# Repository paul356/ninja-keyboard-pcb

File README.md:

# How to use this project?

This pcb use some symbols and footprints that are not in the default KiCad library. I think the fp cache feature should cache these symbols and footprints. But in case you need them.
1. Keyswitch Kicad Library
2. Additional symbols and footprints are in the folder "user_added".

## 3D Case Design

A FreeCAD 3D model of the keyboard case is included in this project: `keyboard-case.FCStd`. You can open it with [FreeCAD](https://www.freecad.org/) to view, modify, or export the case design for 3D printing or CNC machining.

## License

This project is licensed under the [GNU General Public License v3.0](LICENSE).

You are free to use, study, modify, and distribute this project, provided that any derivative works are also distributed under the same GPL-3.0 license.

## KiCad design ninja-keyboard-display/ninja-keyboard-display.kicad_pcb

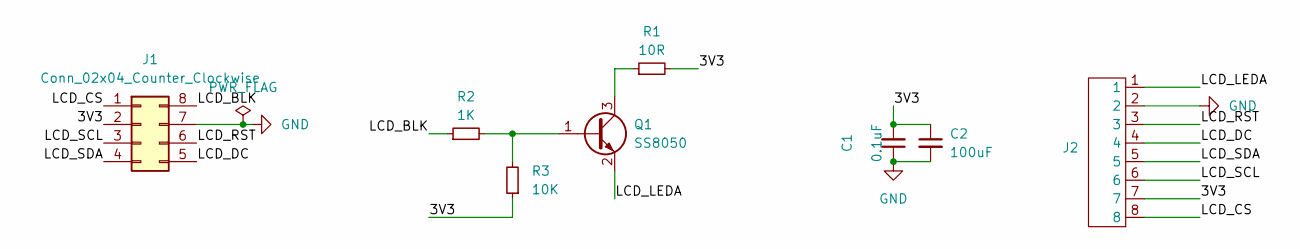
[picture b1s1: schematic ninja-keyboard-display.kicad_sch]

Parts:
C1: 0.1uF; C_0603_1608Metric; LCSC Part # C14663
C2: 100uF; CP_Elec_6.3x7.7
J1: Conn_02x04_Counter_Clockwise; PinHeader_2x04_P2.54mm_Vertical
J2: HanElectricity 1x8 P0.5mm drawer up-side; LCSC Part # C5362163
Q1: SS8050; SOT-23; LCSC Part # C2150
R1: 10R; R_0603_1608Metric; LCSC Part # C22859
R2: 1K; R_0603_1608Metric; LCSC Part # C21190
R3: 10K; R_0603_1608Metric; LCSC Part # C25804

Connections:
/3V3: C1.2, C2.1, J1.2, J2.7, R1.2, R3.1
/LCD_BLK: J1.8, R2.1
/LCD_CS: J1.1, J2.8
/LCD_DC: J1.5, J2.4
/LCD_LEDA: J2.1, Q1.2 (E)
/LCD_RST: J1.6, J2.3
/LCD_SCL: J1.3, J2.6
/LCD_SDA: J1.4, J2.5
GND: C1.1, C2.2, J1.7, J2.2
unnamed: Q1.1 (B), R2.2, R3.2
unnamed: Q1.3 (C), R1.1

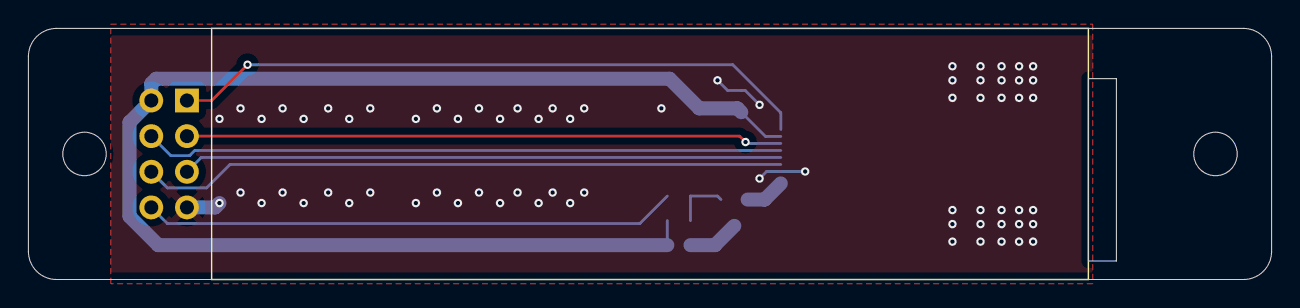
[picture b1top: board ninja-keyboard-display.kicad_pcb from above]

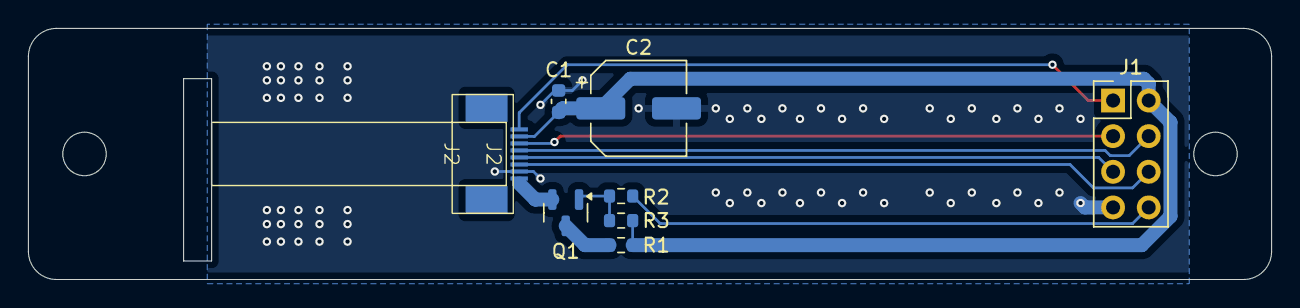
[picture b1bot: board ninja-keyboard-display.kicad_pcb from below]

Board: 2 copper layers, 88.6 x 17.9 mm, 8 parts (8 on the bottom side), 11 nets.

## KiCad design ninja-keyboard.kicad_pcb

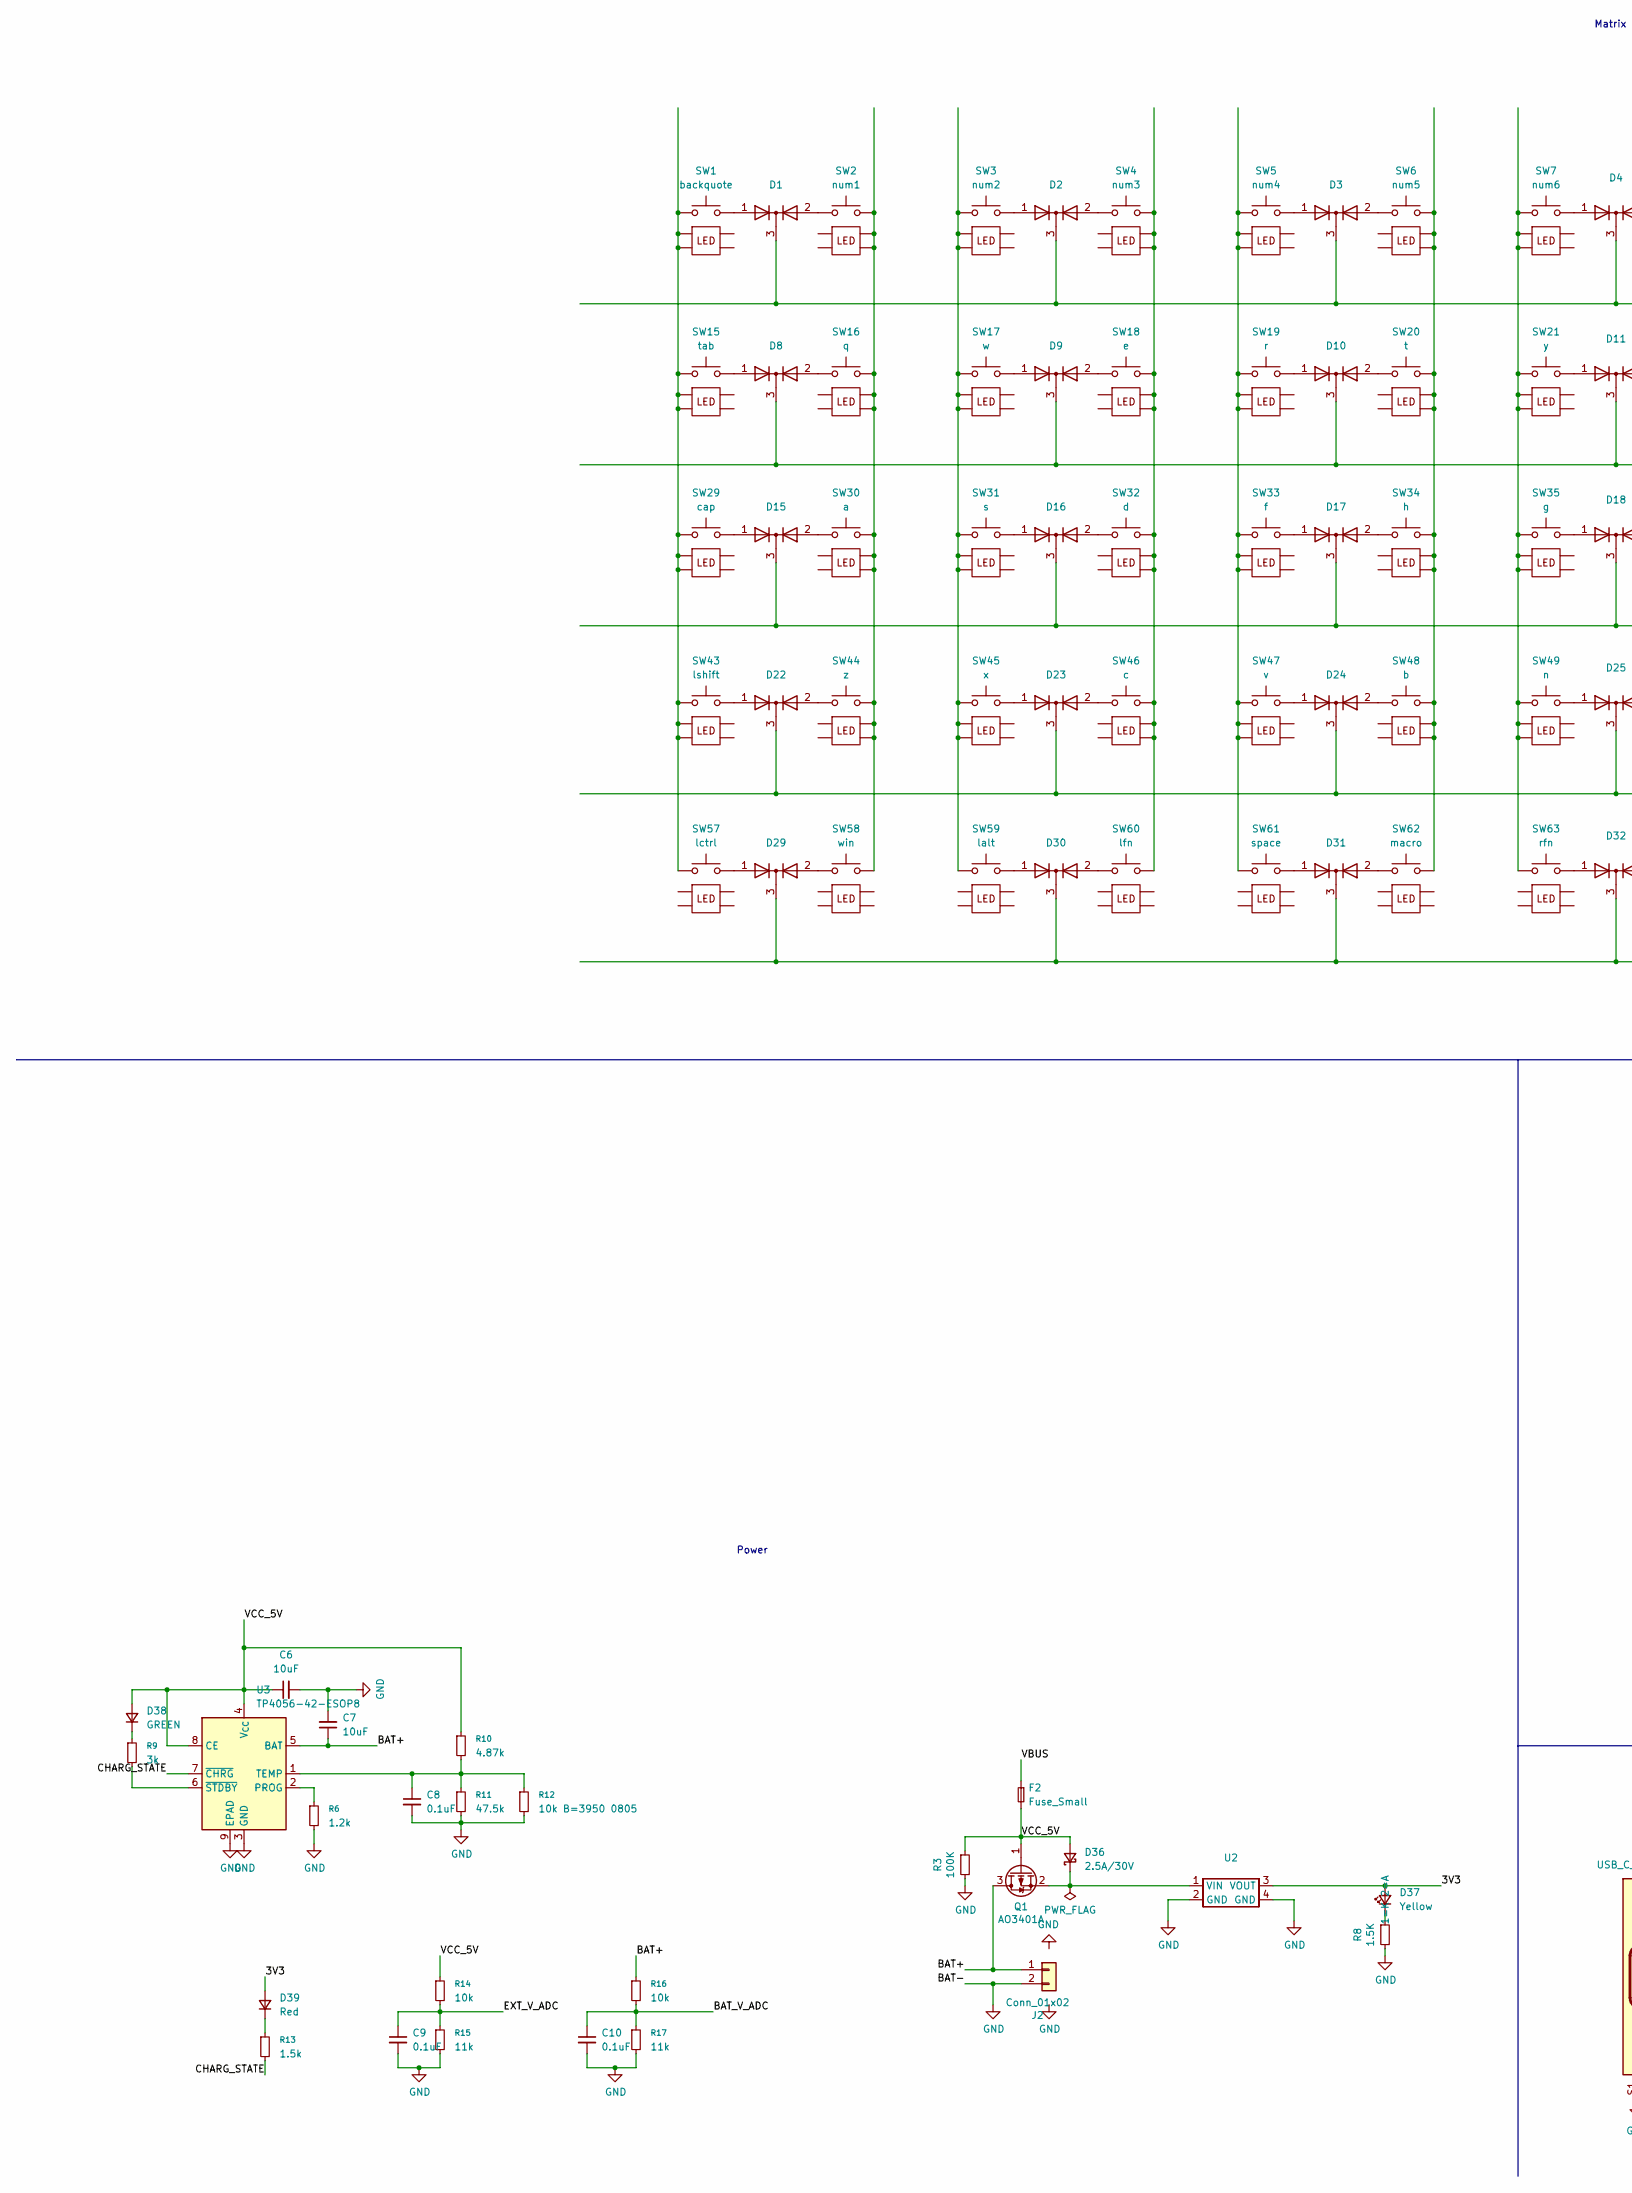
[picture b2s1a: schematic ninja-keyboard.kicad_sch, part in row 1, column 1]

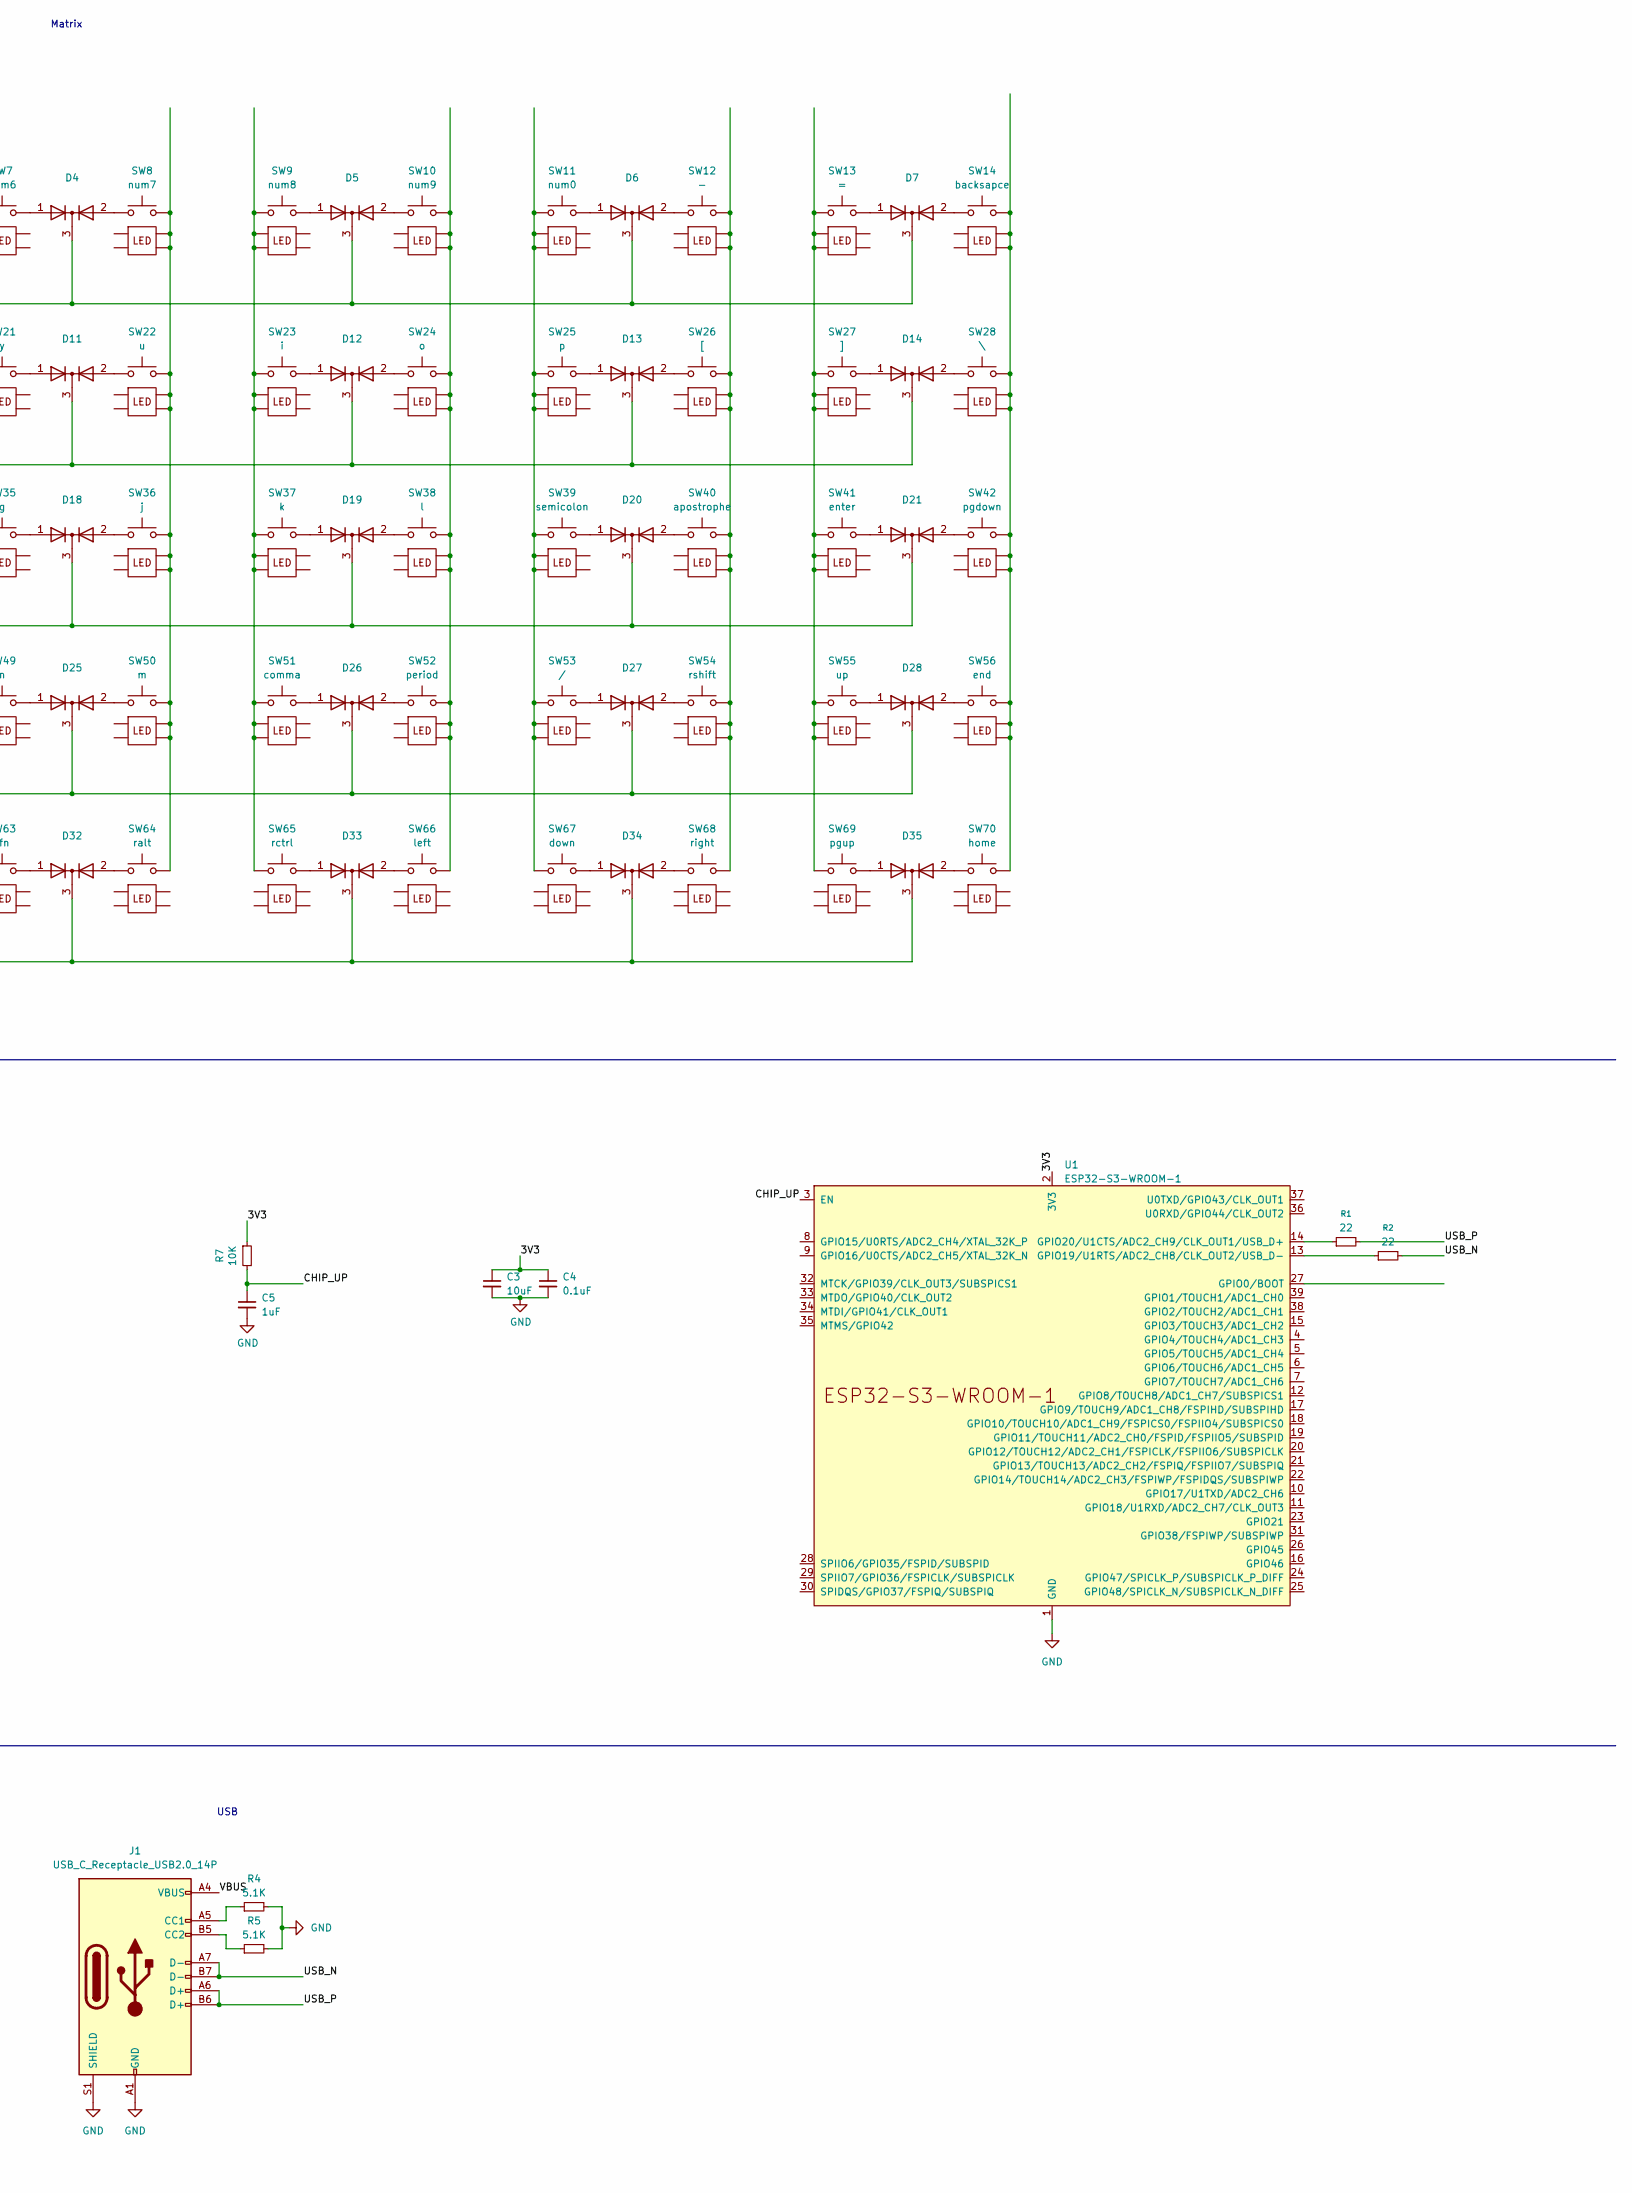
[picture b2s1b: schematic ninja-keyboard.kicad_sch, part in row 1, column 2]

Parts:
C3: 10uF; C_0603_1608Metric; LCSC Part # C19702
C4: 0.1uF; C_0603_1608Metric; LCSC Part # C14663
C5: 1uF; C_0603_1608Metric; LCSC Part # C15849
C6, C7: 10uF; C_0603_1608Metric
C8, C9, C10: 0.1uF; C_0603_1608Metric
D1, D2, D3, D4, D5, D6, D7, D8, D9, D10, D11, D12, D13, D14, D15, D16, D17, D18, D19, D20, D21, D22, D23, D24, D25, D26, D27, D28, D29, D30, D31, D32, D33, D34, D35: SOT-23
D36: 2.5A/30V; D_SOD-123; LCSC Part # C8598
D37: Yellow; LED_0603_1608Metric; LCSC Part # C2286
D38: GREEN; LED_0603_1608Metric
D39: Red; LED_0603_1608Metric
F2: Fuse_Small; Fuse_0805_2012Metric; LCSC Part # C7472578
J1: USB_C_Receptacle_USB2.0_14P; USB_C_Receptacle_HRO_TYPE-C-31-M-12; LCSC Part # C165948
J2: Conn_01x02; PH 1x2 pin gap 2.0mm SMD socket; LCSC Part # C2845379
Q1: AO3401A; SOT-23; LCSC Part # C15127
R1, R2: 22; R_0603_1608Metric
R3: 100K; R_0603_1608Metric; LCSC Part # C25804
R4, R5: 5.1K; R_0603_1608Metric; LCSC Part # C23186
R6: 1.2k; R_0603_1608Metric
R7: 10K; R_0603_1608Metric; LCSC Part # C25804
R8: 1.5K; R_0603_1608Metric; LCSC Part # C25804
R9: 3k; R_0603_1608Metric
R10: 4.87k; R_0603_1608Metric
R11: 47.5k; R_0603_1608Metric
R12: 10k B=3950 0805; R_0805_2012Metric
R13: 1.5k; R_0603_1608Metric
R14, R16: 10k; R_0603_1608Metric
R15, R17: 11k; R_0603_1608Metric
SW1: backquote; SW_Hotswap_Kailh_MX_1.00u with led
SW2: num1; SW_Hotswap_Kailh_MX_1.00u with led
SW3: num2; SW_Hotswap_Kailh_MX_1.00u with led
SW4: num3; SW_Hotswap_Kailh_MX_1.00u with led
SW5: num4; SW_Hotswap_Kailh_MX_1.00u with led
SW6: num5; SW_Hotswap_Kailh_MX_1.00u with led
SW7: num6; SW_Hotswap_Kailh_MX_1.00u with led
SW8: num7; SW_Hotswap_Kailh_MX_1.00u with led
SW9: num8; SW_Hotswap_Kailh_MX_1.00u with led
SW10: num9; SW_Hotswap_Kailh_MX_1.00u with led
SW11: num0; SW_Hotswap_Kailh_MX_1.00u with led
SW12: -; SW_Hotswap_Kailh_MX_1.00u with led
SW13: =; SW_Hotswap_Kailh_MX_1.00u with led
SW14: backsapce; SW_Hotswap_Kailh_MX_1.75u with led
SW15: tab; SW_Hotswap_Kailh_MX_1.50u with led
SW16: q; SW_Hotswap_Kailh_MX_1.00u with led
SW17: w; SW_Hotswap_Kailh_MX_1.00u with led
SW18: e; SW_Hotswap_Kailh_MX_1.00u with led
SW19: r; SW_Hotswap_Kailh_MX_1.00u with led
SW20: t; SW_Hotswap_Kailh_MX_1.00u with led
SW21: y; SW_Hotswap_Kailh_MX_1.00u with led
SW22: u; SW_Hotswap_Kailh_MX_1.00u with led
SW23: i; SW_Hotswap_Kailh_MX_1.00u with led
SW24: o; SW_Hotswap_Kailh_MX_1.00u with led
SW25: p; SW_Hotswap_Kailh_MX_1.00u with led
SW26: [; SW_Hotswap_Kailh_MX_1.00u with led
SW27: ]; SW_Hotswap_Kailh_MX_1.00u with led
SW28: \; SW_Hotswap_Kailh_MX_1.25u with led
SW29: cap; SW_Hotswap_Kailh_MX_1.75u with led
SW30: a; SW_Hotswap_Kailh_MX_1.00u with led
SW31: s; SW_Hotswap_Kailh_MX_1.00u with led
SW32: d; SW_Hotswap_Kailh_MX_1.00u with led
SW33: f; SW_Hotswap_Kailh_MX_1.00u with led
SW34: h; SW_Hotswap_Kailh_MX_1.00u with led
SW35: g; SW_Hotswap_Kailh_MX_1.00u with led
SW36: j; SW_Hotswap_Kailh_MX_1.00u with led
SW37: k; SW_Hotswap_Kailh_MX_1.00u with led
SW38: l; SW_Hotswap_Kailh_MX_1.00u with led
SW39: semicolon; SW_Hotswap_Kailh_MX_1.00u with led
SW40: apostrophe; SW_Hotswap_Kailh_MX_1.00u with led
SW41: enter; SW_Hotswap_Kailh_MX_2.00u with led
SW42: pgdown; SW_Hotswap_Kailh_MX_1.00u with led
SW43: lshift; SW_Hotswap_Kailh_MX_2.25u with led
SW44: z; SW_Hotswap_Kailh_MX_1.00u with led
SW45: x; SW_Hotswap_Kailh_MX_1.00u with led
SW46: c; SW_Hotswap_Kailh_MX_1.00u with led
SW47: v; SW_Hotswap_Kailh_MX_1.00u with led
SW48: b; SW_Hotswap_Kailh_MX_1.00u with led
SW49: n; SW_Hotswap_Kailh_MX_1.00u with led
SW50: m; SW_Hotswap_Kailh_MX_1.00u with led
SW51: comma; SW_Hotswap_Kailh_MX_1.00u with led
SW52: period; SW_Hotswap_Kailh_MX_1.00u with led
SW53: /; SW_Hotswap_Kailh_MX_1.00u with led
SW54: rshift; SW_Hotswap_Kailh_MX_1.50u with led
SW55: up; SW_Hotswap_Kailh_MX_1.00u with led
SW56: end; SW_Hotswap_Kailh_MX_1.00u with led
SW57: lctrl; SW_Hotswap_Kailh_MX_1.25u with led
SW58: win; SW_Hotswap_Kailh_MX_1.25u with led
SW59: lalt; SW_Hotswap_Kailh_MX_1.25u with led
SW60: lfn; SW_Hotswap_Kailh_MX_1.00u with led
SW61: space; SW_Hotswap_Kailh_MX_2.25u with led
SW62: macro; SW_Hotswap_Kailh_MX_2.25u with led
SW63: rfn; SW_Hotswap_Kailh_MX_1.00u with led
SW64: ralt; SW_Hotswap_Kailh_MX_1.25u with led
SW65: rctrl; SW_Hotswap_Kailh_MX_1.25u with led
SW66: left; SW_Hotswap_Kailh_MX_1.00u with led
SW67: down; SW_Hotswap_Kailh_MX_1.00u with led
SW68: right; SW_Hotswap_Kailh_MX_1.00u with led
SW69: pgup; SW_Hotswap_Kailh_MX_1.00u with led
SW70: home; SW_Hotswap_Kailh_MX_1.00u with led
U1: ESP32-S3-WROOM-1
U2: XL63020-3.3
U3: TP4056-42-ESOP8; SOIC-8-1EP_3.9x4.9mm_P1.27mm_EP2.41x3.3mm_ThermalVias

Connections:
/3V3: C3.1, C4.1, D37.2 (A), D39.2 (A), R7.1, U1.2 (3V3), U2.3 (VOUT)
/BAT+: C7.1, J2.1, Q1.3 (D), R16.1, U3.5 (BAT)
/BAT_V_ADC: C10.1, R16.2, R17.1
/CHARG_STATE: R13.2, U3.7 (~CHRG)
/CHIP_UP: C5.1, R7.2, U1.3 (EN)
/EXT_V_ADC: C9.1, R14.2, R15.1
/USB_N: J1.A7 (D-), J1.B7 (D-), R2.2
/USB_P: J1.A6 (D+), J1.B6 (D+), R1.2
/VBUS: F2.1, J1.A4 (VBUS), J1.A9 (VBUS), J1.B4 (VBUS), J1.B9 (VBUS)
/VCC_5V: C6.1, D36.2 (A), D38.2 (A), F2.2, Q1.1 (G), R3.1, R10.1, R14.1, U3.4 (V_{CC}), U3.8 (CE)
GND: C3.2, C4.2, C5.2, C6.2, C7.2, C8.2, C9.2, C10.2, J1.A1 (GND), J1.A12 (GND), J1.B1 (GND), J1.B12 (GND), J1.S1 (SHIELD), J2.2, R3.2, R4.2, R5.2, R6.2, R8.2, R11.2, R12.2, R15.2, R17.2, U1.1 (GND), U1.40 (GND), U1.41 (GND), U2.2 (GND), U2.4 (GND), U3.3 (GND), U3.9 (EPAD)
unnamed: D1.1 (A), SW1.2
unnamed: D1.2 (A), SW2.1
unnamed: D1.3 (K), D2.3 (K), D3.3 (K), D4.3 (K), D5.3 (K), D6.3 (K), D7.3 (K)
unnamed: D2.1 (A), SW3.2
unnamed: D2.2 (A), SW4.1
unnamed: D3.1 (A), SW5.2
unnamed: D3.2 (A), SW6.1
unnamed: D4.1 (A), SW7.2
unnamed: D4.2 (A), SW8.1
unnamed: D5.1 (A), SW9.2
unnamed: D5.2 (A), SW10.1
unnamed: D6.1 (A), SW11.2
unnamed: D6.2 (A), SW12.1
unnamed: D7.1 (A), SW13.2
unnamed: D7.2 (A), SW14.1
unnamed: D8.1 (A), SW15.2
unnamed: D8.2 (A), SW16.1
unnamed: D9.1 (A), SW17.2
unnamed: D9.2 (A), SW18.1
unnamed: D10.1 (A), SW19.2
unnamed: D10.2 (A), SW20.1
unnamed: D8.3 (K), D9.3 (K), D10.3 (K), D11.3 (K), D12.3 (K), D13.3 (K), D14.3 (K)
unnamed: D11.1 (A), SW21.2
unnamed: D11.2 (A), SW22.1
unnamed: D12.1 (A), SW23.2
unnamed: D12.2 (A), SW24.1
unnamed: D13.1 (A), SW25.2
unnamed: D13.2 (A), SW26.1
unnamed: D14.1 (A), SW27.2
unnamed: D14.2 (A), SW28.1
unnamed: D15.1 (A), SW29.2
unnamed: D15.2 (A), SW30.1
unnamed: D15.3 (K), D16.3 (K), D17.3 (K), D18.3 (K), D19.3 (K), D20.3 (K), D21.3 (K)
unnamed: D16.1 (A), SW31.2
unnamed: D16.2 (A), SW32.1
unnamed: D17.1 (A), SW33.2
unnamed: D17.2 (A), SW34.1
unnamed: D18.1 (A), SW35.2
unnamed: D18.2 (A), SW36.1
unnamed: D19.1 (A), SW37.2
unnamed: D19.2 (A), SW38.1
unnamed: D20.1 (A), SW39.2
unnamed: D20.2 (A), SW40.1
unnamed: D21.1 (A), SW41.2
unnamed: D21.2 (A), SW42.1
unnamed: D22.1 (A), SW43.2
unnamed: D22.2 (A), SW44.1
unnamed: D22.3 (K), D23.3 (K), D24.3 (K), D25.3 (K), D26.3 (K), D27.3 (K), D28.3 (K)
unnamed: D23.1 (A), SW45.2
unnamed: D23.2 (A), SW46.1
unnamed: D24.1 (A), SW47.2
unnamed: D24.2 (A), SW48.1
unnamed: D25.1 (A), SW49.2
unnamed: D25.2 (A), SW50.1
unnamed: D26.1 (A), SW51.2
unnamed: D26.2 (A), SW52.1
unnamed: D27.1 (A), SW53.2
unnamed: D27.2 (A), SW54.1
unnamed: D28.1 (A), SW55.2
unnamed: D28.2 (A), SW56.1
unnamed: D29.1 (A), SW57.2
unnamed: D29.2 (A), SW58.1
unnamed: D29.3 (K), D30.3 (K), D31.3 (K), D32.3 (K), D33.3 (K), D34.3 (K), D35.3 (K)
unnamed: D30.1 (A), SW59.2
unnamed: D30.2 (A), SW60.1
unnamed: D31.1 (A), SW61.2
unnamed: D31.2 (A), SW62.1
unnamed: D32.1 (A), SW63.2
unnamed: D32.2 (A), SW64.1
unnamed: D33.1 (A), SW65.2
unnamed: D33.2 (A), SW66.1
unnamed: D34.1 (A), SW67.2
unnamed: D34.2 (A), SW68.1
unnamed: D35.1 (A), SW69.2
unnamed: D35.2 (A), SW70.1
unnamed: D36.1 (K), Q1.2 (S), U2.1 (VIN)
unnamed: D37.1 (K), R8.1
unnamed: D38.1 (K), R9.1
unnamed: D39.1 (K), R13.1
unnamed: J1.A5 (CC1), R4.1
unnamed: J1.B5 (CC2), R5.1
unnamed: SW1.1, SW1.3 (VDD), SW1.4 (DOUT), SW15.1, SW15.3 (VDD), SW15.4 (DOUT), SW29.1, SW29.3 (VDD), SW29.4 (DOUT), SW43.1, SW43.3 (VDD), SW43.4 (DOUT), SW57.1
unnamed: SW10.2, SW10.5 (DIN), SW10.6 (GND), SW24.2, SW24.5 (DIN), SW24.6 (GND), SW38.2, SW38.5 (DIN), SW38.6 (GND), SW52.2, SW52.5 (DIN), SW52.6 (GND), SW66.2
unnamed: SW11.1, SW11.3 (VDD), SW11.4 (DOUT), SW25.1, SW25.3 (VDD), SW25.4 (DOUT), SW39.1, SW39.3 (VDD), SW39.4 (DOUT), SW53.1, SW53.3 (VDD), SW53.4 (DOUT), SW67.1
unnamed: SW12.2, SW12.5 (DIN), SW12.6 (GND), SW26.2, SW26.5 (DIN), SW26.6 (GND), SW40.2, SW40.5 (DIN), SW40.6 (GND), SW54.2, SW54.5 (DIN), SW54.6 (GND), SW68.2
unnamed: SW13.1, SW13.3 (VDD), SW13.4 (DOUT), SW27.1, SW27.3 (VDD), SW27.4 (DOUT), SW41.1, SW41.3 (VDD), SW41.4 (DOUT), SW55.1, SW55.3 (VDD), SW55.4 (DOUT), SW69.1
unnamed: SW14.2, SW14.5 (DIN), SW14.6 (GND), SW28.2, SW28.5 (DIN), SW28.6 (GND), SW42.2, SW42.5 (DIN), SW42.6 (GND), SW56.2, SW56.5 (DIN), SW56.6 (GND), SW70.2
unnamed: SW2.2, SW2.5 (DIN), SW2.6 (GND), SW16.2, SW16.5 (DIN), SW16.6 (GND), SW30.2, SW30.5 (DIN), SW30.6 (GND), SW44.2, SW44.5 (DIN), SW44.6 (GND), SW58.2
unnamed: SW3.1, SW3.3 (VDD), SW3.4 (DOUT), SW17.1, SW17.3 (VDD), SW17.4 (DOUT), SW31.1, SW31.3 (VDD), SW31.4 (DOUT), SW45.1, SW45.3 (VDD), SW45.4 (DOUT), SW59.1
unnamed: SW4.2, SW4.5 (DIN), SW4.6 (GND), SW18.2, SW18.5 (DIN), SW18.6 (GND), SW32.2, SW32.5 (DIN), SW32.6 (GND), SW46.2, SW46.5 (DIN), SW46.6 (GND), SW60.2
unnamed: SW5.1, SW5.3 (VDD), SW5.4 (DOUT), SW19.1, SW19.3 (VDD), SW19.4 (DOUT), SW33.1, SW33.3 (VDD), SW33.4 (DOUT), SW47.1, SW47.3 (VDD), SW47.4 (DOUT), SW61.1
unnamed: SW6.2, SW6.5 (DIN), SW6.6 (GND), SW20.2, SW20.5 (DIN), SW20.6 (GND), SW34.2, SW34.5 (DIN), SW34.6 (GND), SW48.2, SW48.5 (DIN), SW48.6 (GND), SW62.2
unnamed: SW7.1, SW7.3 (VDD), SW7.4 (DOUT), SW21.1, SW21.3 (VDD), SW21.4 (DOUT), SW35.1, SW35.3 (VDD), SW35.4 (DOUT), SW49.1, SW49.3 (VDD), SW49.4 (DOUT), SW63.1
unnamed: SW8.2, SW8.5 (DIN), SW8.6 (GND), SW22.2, SW22.5 (DIN), SW22.6 (GND), SW36.2, SW36.5 (DIN), SW36.6 (GND), SW50.2, SW50.5 (DIN), SW50.6 (GND), SW64.2
unnamed: SW9.1, SW9.3 (VDD), SW9.4 (DOUT), SW23.1, SW23.3 (VDD), SW23.4 (DOUT), SW37.1, SW37.3 (VDD), SW37.4 (DOUT), SW51.1, SW51.3 (VDD), SW51.4 (DOUT), SW65.1
unnamed: R2.1, U1.13 (GPIO19/U1RTS/ADC2_CH8/CLK_OUT2/USB_D-)
unnamed: R1.1, U1.14 (GPIO20/U1CTS/ADC2_CH9/CLK_OUT1/USB_D+)
unnamed: R6.1, U3.2 (PROG)
unnamed: C8.1, R10.2, R11.1, R12.1, U3.1 (TEMP)
unnamed: R9.2, U3.6 (~STDBY)

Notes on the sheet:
Power
Matrix
USB

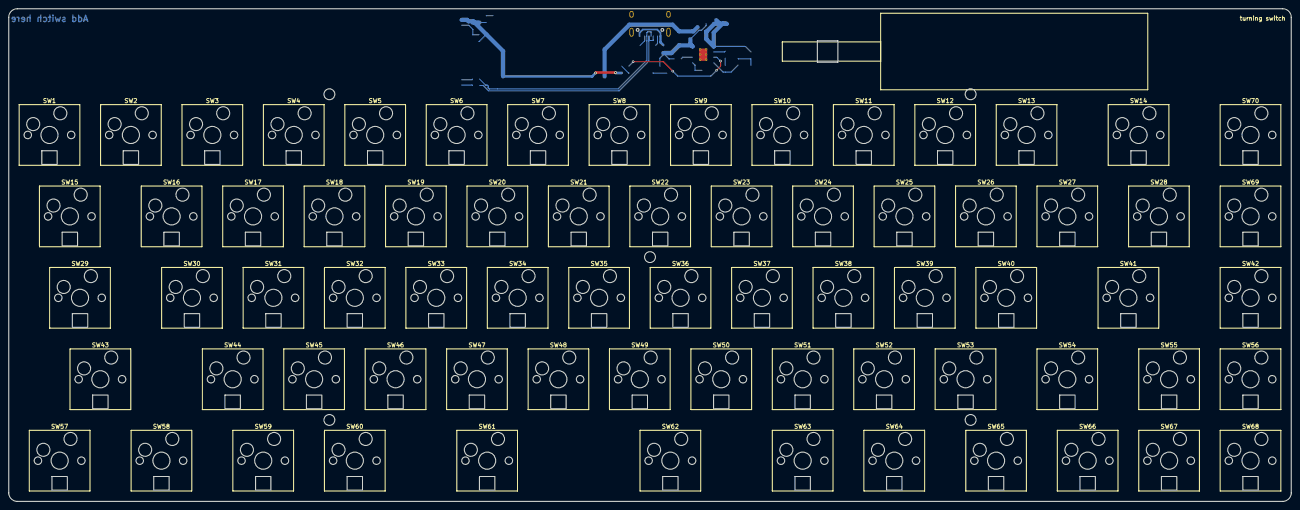
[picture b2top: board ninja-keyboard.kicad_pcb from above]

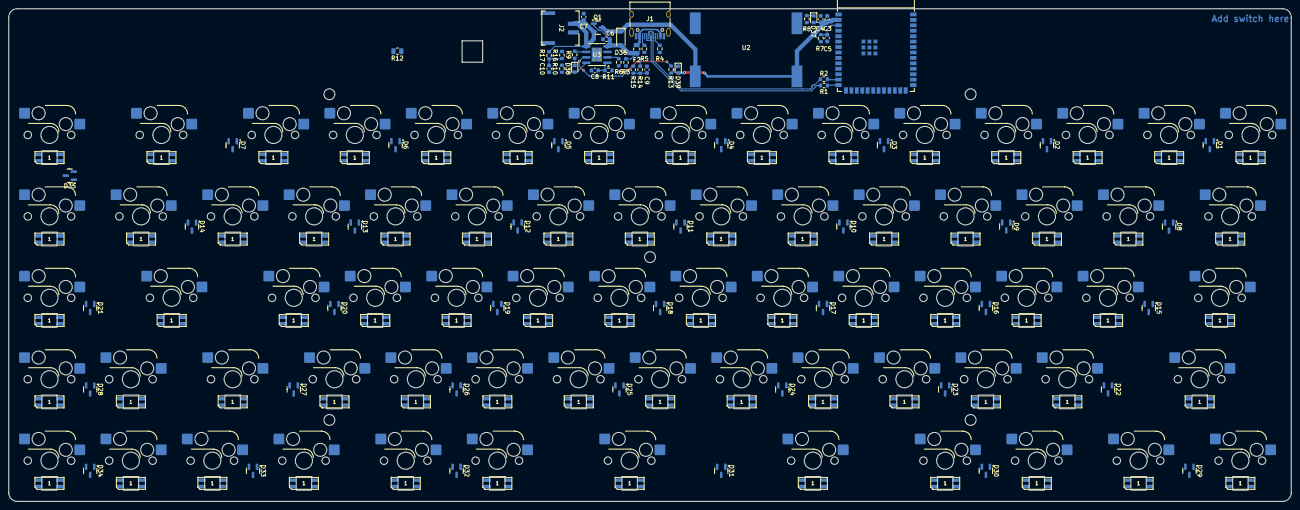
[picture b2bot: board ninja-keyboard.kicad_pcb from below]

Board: 2 copper layers, 300.0 x 115.3 mm, 141 parts (71 on the bottom side), 111 nets.
